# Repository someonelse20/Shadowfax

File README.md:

# Shadowfax
FPV Drone designed from scrach. This design isn't fully custom yet but will get there eventually. I started this project to make a cool drone and learn as much as I can about engineering.

## Flight Controller
The meat and potatios, the main computer for the drone.

## Transceiver
A low frequency radio to communicate with a remote controller.

## Camera Controller
Controls the camera and captures videos and pictures with a high frequency radio for faster communication.

## Power Board
Powers the whole stack with 3.3v and connects the ESCs to the input voltage.

## Frame
I made a custom frame to fit my custom boards and here it is.

## BOM
| Name                       | Purpose                                       | Quantity | Total Cost (USD) | Link               | Distributor |
|----------------------------|-----------------------------------------------|----------|------------------|--------------------|-------------|
| Flight Controller Assembly | Assemble components for the flight controller | 2        | 42.44            | https://jlcpcb.com | JLCPCB      |
| Flight Controller Board    | The pcb for the flight controller             | 5        | 2.00             | https://jlcpcb.com | JLCPCB      |
| Power Board Assembly       | Assemble components for the power board       | 2        | 14.79            | https://jlcpcb.com | JLCPCB      |
| Power Board                | The pcb for the power board                   | 5        | 7.00             | https://jlcpcb.com | JLCPCB      |
| Transceiver Assmebly       | Assemble components for the board             | 2        | 51.31            | https://jlcpcb.com | JLCPCB      |
| Transceiver Board          | The pcb for the transceiver                   | 5        | 7.00             | https://jlcpcb.com | JLCPCB      |
| Camera Controller Assembly | Assemble components for the board             | 2        | 34.63            | https://jlcpcb.com | JLCPCB      |
| Camera Controller Board    | The pcb for the camera controller             | 5        | 7.00             | https://jlcpcb.com | JLCPCB      |

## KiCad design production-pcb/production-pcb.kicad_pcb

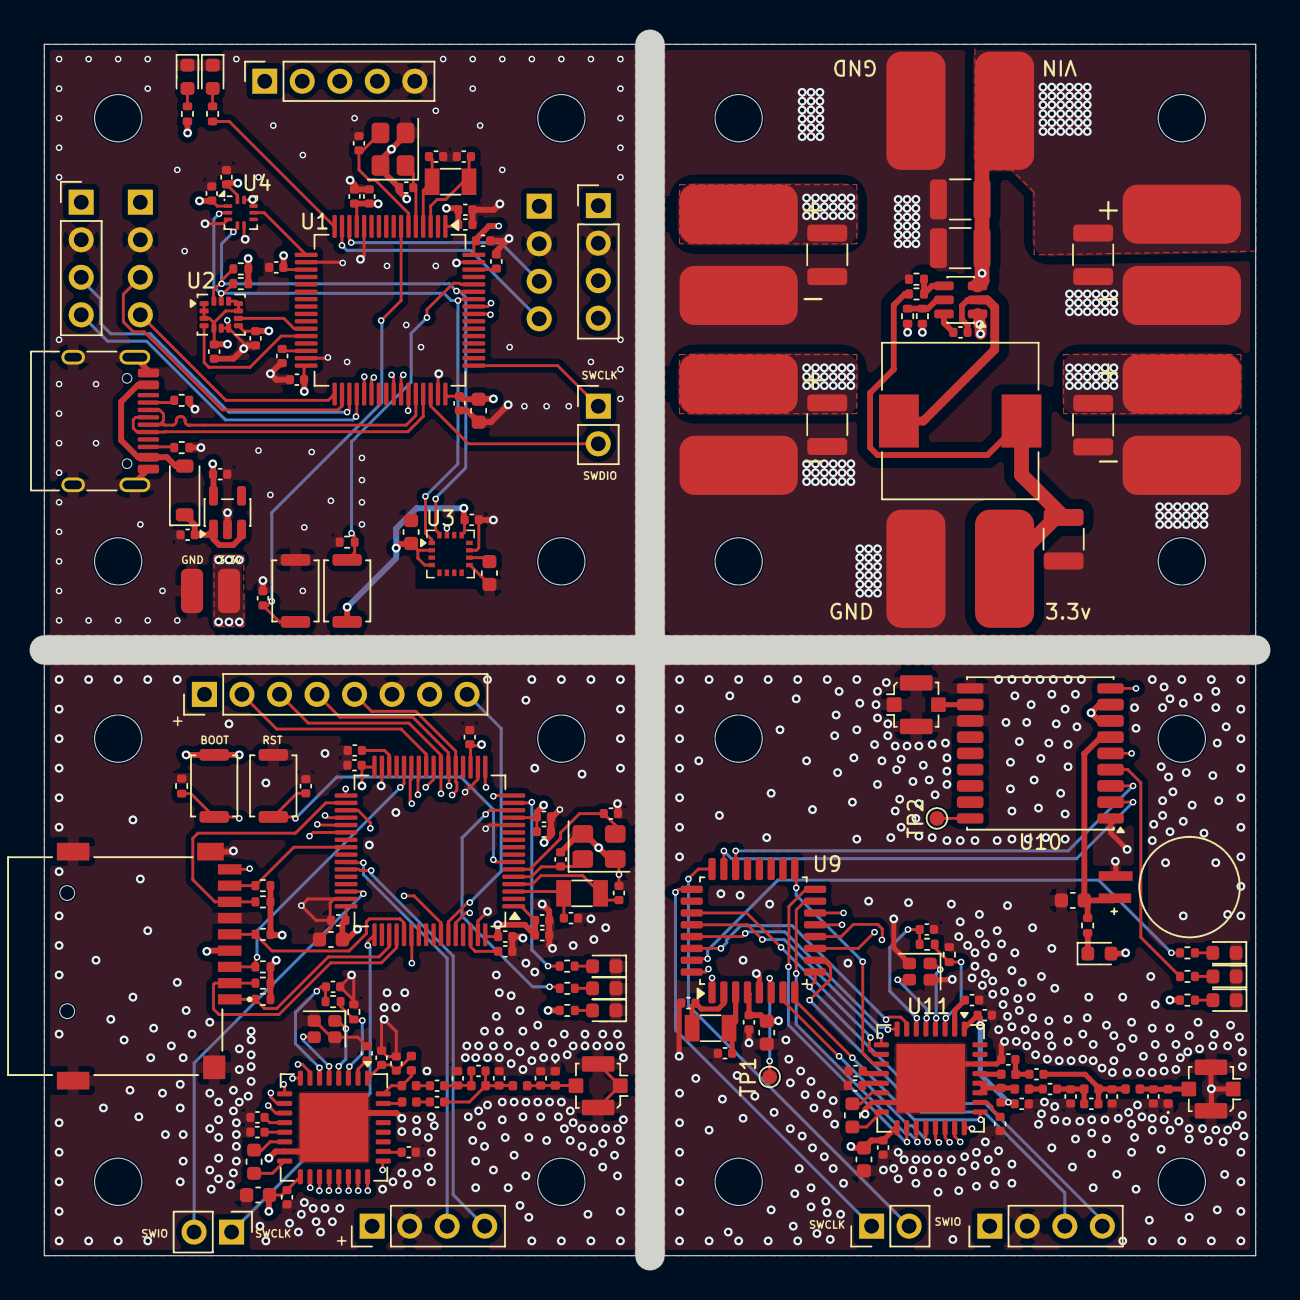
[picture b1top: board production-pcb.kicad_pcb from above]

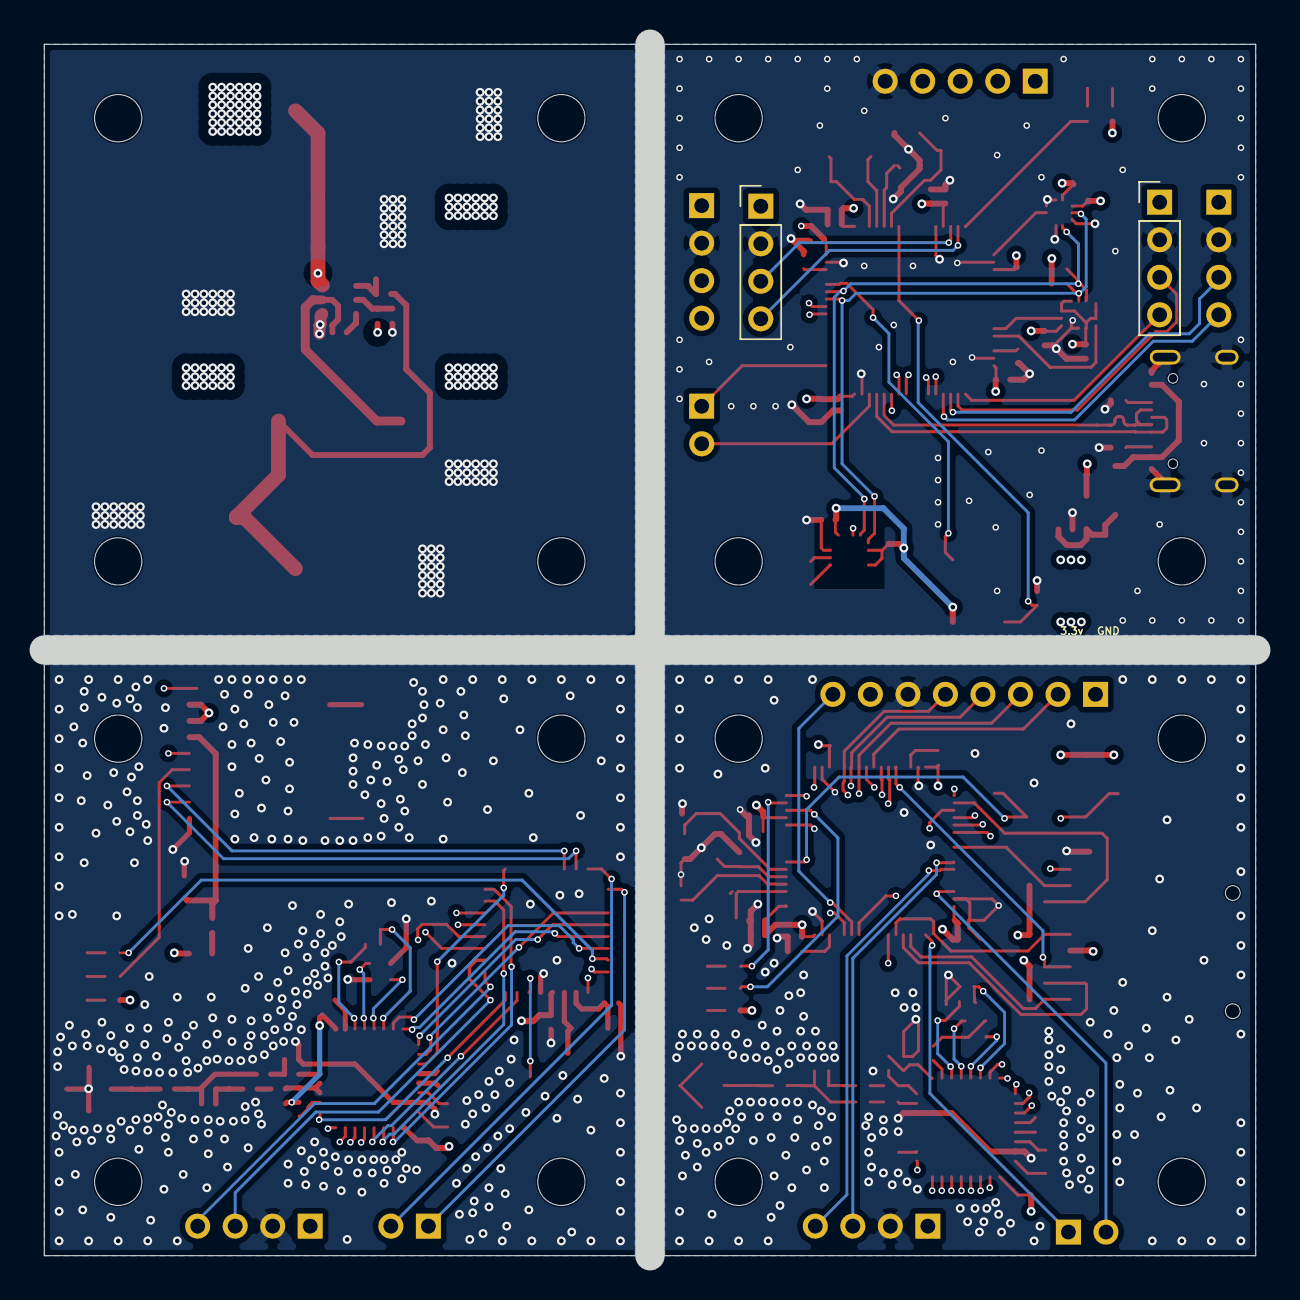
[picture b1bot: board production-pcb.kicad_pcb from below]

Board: 4 copper layers, 82.0 x 82.0 mm, 194 parts (2 on the bottom side), 109 nets.

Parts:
BOOT1, BOOT2: SW_Push; SW_Push_SPST_NO_Alps_SKRK
BT1: MS621FE-FL11E; BAT_MS621FE-FL11E
C1, C74: 1uF; C_0603_1608Metric
C2, C3, C15, C16, C17, C31: 10uF; C_1210_3225Metric
C4, C6, C7, C8, C11, C12, C18, C20, C24, C25, C27, C29, C32, C40, C42, C43, C45, C46, C47, C48, C50, C53, C65, C69, C70: 100nF; C_0402_1005Metric
C5: 10uF; C_0603_1608Metric
C9, C14, C34, C37, C57, C83: 18pF; C_0402_1005Metric
C10, C13, C35, C36: 15pF; C_0402_1005Metric
C19, C21, C22, C23, C41, C44, C61, C63, C75, C76: 1uF; C_0402_1005Metric
C26, C28, C38, C39, C58, C60, C72, C73: 2.2uF; C_0402_1005Metric
C30, C49, C55, C66, C71: 4.7uF; C_0603_1608Metric
C33: 47uF; C_1210_3225Metric
C51, C67, C68, C78: 47pF; C_0402_1005Metric
C52: 6.8pF; C_0402_1005Metric
C54: 2.7pF; C_0402_1005Metric
C56: 1.1pF; C_0402_1005Metric
C59: 1.2pF; C_0402_1005Metric
C62: 2pF; C_0402_1005Metric
C64, C77: 1nF; C_0402_1005Metric
C79: 22pF; C_0402_1005Metric
C80: 2.2pF; C_0402_1005Metric
C81: 7.5pF; C_0402_1005Metric
C82, C85: 1.8pF; C_0402_1005Metric
C84: 3.9pF; C_0402_1005Metric
D1, D2, D4, D5, D6, D9, D10, D11: LED; LED_0603_1608Metric
D3: D_Schottky; D_SOD-123
D7, D12: D_TVS; D_0402_1005Metric
D8: D_Schottky; D_0603_1608Metric
J1: USB_C_Receptacle_USB2.0_14P; USB_C_Receptacle_HRO_TYPE-C-31-M-12
J2, J3, J3#2, J4#2, J5, J22: Conn_01x04; PinHeader_1x04_P2.54mm_Vertical
J4, J7, J24: Conn_01x02; PinHeader_1x02_P2.54mm_Vertical
J6: Conn_01x05; PinSocket_1x05_P2.54mm_Vertical
J8, J9: Conn_01x01; SolderWirePad_1x01_SMD_1.5x3mm
J10, J11, J12, J13, J14, J15, J16, J17, J18, J19, J20, J21: Conn_01x01; SolderWirePad_1x01_SMD_4x8mm
J23: Conn_01x08; PinHeader_1x08_P2.54mm_Vertical
J25: Micro_SD_Card_Det1; CUI_MSD-4-A
J26, J29, J30: Conn_Coaxial; U.FL_Molex_MCRF_73412-0110_Vertical
L1: 10uH; L_10.4x10.4_H4.8
L2: 18nH; L_0402_1005Metric
L3: 1.5nH; L_0402_1005Metric
L4: 1.6nH; L_0402_1005Metric
L5: 1.1nH; L_0402_1005Metric
L6, L8: 2.2uH; L_0603_1608Metric
L7: 2.4nH; L_0402_1005Metric
L9: 12nH; L_0402_1005Metric
L10: 4.7nH; L_0402_1005Metric
L11: 24nH; L_0402_1005Metric
L12: 3.9nH; L_0402_1005Metric
L13: 7.5nH; L_0402_1005Metric
R1, R2: 5.1K; R_0402_1005Metric
R3, R10, R11, R12, R14, R16, R17, R21: 10K; R_0402_1005Metric
R4, R5, R18, R19, R20, R25, R26, R27: 1.2K; R_0402_1005Metric
R6, R8: 100K; R_0402_1005Metric
R7: 33.2K; R_0402_1005Metric
R9: 22K; R_0402_1005Metric
R13, R15, R24: 1K; R_0402_1005Metric
R22, R23: 120K; R_0402_1005Metric
RESET1, RESET2: SW_Push; SW_Push_SPST_NO_Alps_SKRK
TH1, TH2: ERT-J0ER104F; R_0402_1005Metric
TP1, TP2: TestPoint; TestPoint_Pad_D1.0mm
U1, U7: STM32H523RCTx; LQFP-64_10x10mm_P0.5mm
U2: LSM6DSV; LGA-14_3x2.5mm_P0.5mm_LayoutBorder3x4y
U3: MMC5983MA; LGA-16_3x3mm_P0.5mm
U4: BMP384; Rohm_MLGA010V020A_LGA-10_2x2mm_P0.45mm_LayoutBorder2x3y
U5: MIC5504-3.3YM5; SOT-23-5
U6: TPS54308; SOT-23-6
U8, U11: LR2021; QFN-32-1EP_7x7mm_P0.65mm_EP4.65x4.65mm
U9: STM32G030K8Tx; LQFP-32_7x7mm_P0.8mm
U10: MAX-M10S; ublox_MAX
Y1, Y3: 32.768MHz; Crystal_SMD_3215-2Pin_3.2x1.5mm
Y2, Y4: 24MHz; Crystal_SMD_3225-4Pin_3.2x2.5mm
Y5, Y7: 32MHz 10pF; Crystal_SMD_2016-4Pin_2.0x1.6mm
Y6: 32.768KHz; Crystal_SMD_3215-2Pin_3.2x1.5mm

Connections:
+3.3V: BOOT1.1, BOOT2.1, C1.1, C4.1, C6.1, C7.1, C8.1, C12.1, C18.1, C19.1, C20.1, C21.1, C23.1, C24.1, C25.1, C27.1, C29.1, C30.1, C40.1, C41.1, C42.1, C44.1, C45.1, C46.1, C47.1, C48.1, C49.1, C53.1, C55.1, C65.1, C66.1, C70.1, C71.1, D8.2 (A), J2.1, J3.1, J3#2.1, J4#2.1, J5.1, J8.1 (Pin_1_1), J22.1, J23.7, J25.4 (VDD), R4.1, R5.1, R10.1, R11.1, R12.1, R14.1, R15.1, R16.1, R17.1, R18.1, R25.1, U1.1 (VBAT), U1.13 (VDDA), U1.19 (VDD), U1.32 (VDD), U1.48 (VDD), U1.64 (VDD), U2.1 (SDO/SA0), U2.2 (SDX), U2.3 (SCX), U2.5 (VDDIO), U2.8 (VDD), U2.10 (OCS_Aux), U2.11 (SDO_Aux), U2.12 (CS), U3.2 (VDD), U3.4 (SPI_CS), U3.13 (VDDIO), U4.1 (VDDIO), U4.10 (VDD), U5.5 (VOUT), U7.1 (VBAT), U7.13 (VDDA), U7.19 (VDD), U7.32 (VDD), U7.48 (VDD), U7.64 (VDD), U8.17 (VBAT), U9.4 (VDD), U10.7 (VCC_IO), U10.8 (VCC), U11.17 (VBAT)
/BMP_INT: U1.17 (PA3), U4.7 (INT)
/BOOT: BOOT1.2, BOOT2.2, R3.1, R21.1, U1.60 (BOOT0), U7.60 (BOOT0)
/CAM_CS: J23.2, U7.25 (PC5)
/CAM_STAT: R19.1, U7.14 (PA0)
/ESC1: J6.1, U1.41 (PA8)
/ESC2: J6.2, U1.42 (PA9)
/ESC3: J6.3, U1.56 (PB4(NJTRST))
/ESC4: J6.4, U1.57 (PB5)
/GPS_INT: U9.32 (PB8), U10.5 (EXTINT)
/GPS_LED: R26.1, U10.4 (TIMEPULSE)
/GPS_RST: U9.1 (PB9), U10.9 (~RESET)
/GPS_RX: U9.23 (PA10/PA12), U10.2 (TXD)
/GPS_TX: U9.22 (PA9/PA11), U10.3 (RXD)
/HSE_IN: C9.1, C37.1, U1.5 (PH0), U7.5 (PH0), Y2.1, Y4.1
/HSE_OUT: C14.1, C34.1, U1.6 (PH1), U7.6 (PH1), Y2.3, Y4.3
/LMS_INT2: U1.27 (PB1), U2.9 (INT2)
/LR_BUSY: U7.16 (PA2), U8.25 (BUSY), U9.8 (PA1), U11.25 (BUSY)
/LR_CS: U7.17 (PA3), U8.24 (NSS)
/LR_D5: U7.26 (PB0), U8.19 (DIO5), U9.15 (PB0), U11.19 (DIO5)
/LR_D6: U7.27 (PB1), U8.18 (DIO6), U9.16 (PB1), U11.18 (DIO6)
/LR_D7: U7.38 (PC7), U8.11 (DIO7), U9.17 (PB2), U11.11 (DIO7)
/LR_D8: U7.37 (PC6), U8.10 (DIO8), U9.27 (PB3), U11.10 (DIO8)
/LR_D9: U7.36 (PB15), U8.9 (DIO9), U9.28 (PB4), U11.9 (DIO9)
/LR_D10: U7.35 (PB14), U8.8 (DIO10), U9.29 (PB5), U11.8 (DIO10)
/LR_D11: U7.33 (PB12), U8.7 (DIO11), U9.30 (PB6), U11.7 (DIO11)
/LR_RST: U7.24 (PC4), U8.20 (~RESET), U9.7 (PA0), U11.20 (~RESET)
/LR_STAT: R20.1, R27.1, U7.15 (PA1), U9.31 (PB7)
/LSE_IN: C10.1, C35.1, C67.2, U1.3 (PC14), U7.3 (PC14), U9.2 (PC14), Y1.1, Y3.1, Y6.2
/LSE_OUT: C13.1, C36.1, C68.2, U1.4 (PC15), U7.4 (PC15), U9.3 (PC15), Y1.2, Y3.2, Y6.1
/LSM_INT1: U1.28 (PB2), U2.4 (INT1)
/MISO: J23.4, U7.22 (PA6), U8.21 (MISO), U9.13 (PA6), U11.21 (MISO)
/MMC_INT: U1.43 (PA10), U3.15 (INT)
/MOSI: J23.3, U7.23 (PA7), U8.22 (MOSI), U9.14 (PA7), U11.22 (MOSI)
/NSS: U9.11 (PA4), U11.24 (NSS)
/NTC: R22.2, R23.2, TH1.1, TH2.1, U8.3 (NTC), U11.3 (NTC)
/RFI: L7.1, U8.31 (RFI_HF)
/RFI_LF: L11.1, U11.29 (RFI_LF)
/RFO: L2.2, L3.1, U8.32 (RFO_HF)
/RFO_LF1: L9.2, L10.1, U11.27 (RFO_LF2), U11.28 (RFO_LF1)
/SCK: J23.5, U7.21 (PA5), U8.23 (SCK), U9.12 (PA5), U11.23 (SCK)
/SCL: J23.1, R4.2, U1.58 (PB6), U2.13 (SCL), U3.1 (SCL/SPI_SCK), U4.2 (SCK), U7.58 (PB6)
/SDA: J23.8, R5.2, U1.59 (PB7), U2.14 (SDA), U3.16 (SDA/SPI_SDI), U4.4 (SDI), U7.59 (PB7)
/SD_CLK: J25.5 (CLK), R14.2, U7.53 (PC12)
/SD_CMD: J25.3 (CMD), R12.2, U7.28 (PB2)
/SD_D0: J25.7 (DAT0), R16.2, U7.34 (PB13)
/SD_D1: J25.8 (DAT1), R17.2, U7.40 (PC9)
/SD_D2: J25.1 (DAT2), R10.2, U7.51 (PC10)
/SD_D3: J25.2 (DAT3/CD), R11.2, U7.52 (PC11)
/SD_DET: J25.9 (DET), U7.54 (PD2)
/STAT_LED: R13.1, U1.16 (PA2)
/STM32_RST: C11.2, C43.2, RESET1.2, RESET2.2, U1.7 (NRST), U7.7 (NRST)
/SWCLK: J4.1, J7.1, J24.1, U1.49 (PA14(JTCK), U7.49 (PA14(JTCK), U9.25 (PA14)
/SWDIO: J4.2, J7.2, J24.2, U1.46 (PA13(JTMS), U7.46 (PA13(JTMS), U9.24 (PA13)
/UART_RX: J3.3, J22.3, U7.42 (PA9), U9.10 (PA3)
/UART_RX1: J2.4, U1.36 (PB15)
/UART_RX4: J4#2.4, U1.15 (PA1)
/UART_RX5: J3#2.4, U1.33 (PB12)
/UART_RX6: J5.4, U1.38 (PC7)
/UART_TX: J3.4, J22.4, U7.43 (PA10), U9.9 (PA2)
/UART_TX1: J2.3, U1.35 (PB14)
/UART_TX4: J4#2.3, U1.14 (PA0)
/UART_TX5: J3#2.3, U1.34 (PB13)
/UART_TX6: J5.3, U1.37 (PC6)
/USB_+: J1.A6 (D+), J1.B6 (D+), U1.45 (PA12), U7.45 (PA12)
/USB_-: J1.A7 (D-), J1.B7 (D-), U1.44 (PA11), U7.44 (PA11)
/VDCC1: C63.1, C76.1, U8.12 (VDCC1), U11.12 (VDCC1)
/VDCC2: C61.1, C75.1, U8.26 (VDCC2), U11.26 (VDCC2)
/VNTC: C50.1, C69.1, R22.1, R23.1, U8.6 (VTCXO/VNTC), U11.6 (VTCXO/VNTC)
/VPAX1: C60.1, C73.1, U8.13 (VPAX1), U11.13 (VPAX1)
/VPAX2: C58.1, C72.1, U8.2 (VPAX2), U11.2 (VPAX2)
/VR_PA: C51.1, C64.1, C77.1, C78.1, L2.1, L9.1, U8.1 (VR_PA), U11.1 (VR_PA)
/V_BCKP: BT1.1 (+), C74.1, R24.2, U10.6 (V_BCKP)
GND: BT1.2 (-), C1.2, C2.2, C3.2, C4.2, C5.2, C6.2, C7.2, C8.2, C9.2, C10.2, C11.1, C12.2, C13.2, C14.2, C15.2, C16.2, C17.2, C18.2, C19.2, C20.2, C21.2, C22.2, C23.2, C24.2, C25.2, C26.2, C27.2, C28.2, C29.2, C30.2, C31.2, C33.2, C34.2, C35.2, C36.2, C37.2, C38.2, C39.2, C40.2, C41.2, C42.2, C43.1, C44.2, C45.2, C46.2, C47.2, C48.2, C49.2, C50.2, C51.2, C53.2, C54.2, C55.2, C58.2, C59.2, C60.2, C61.2, C62.2, C63.2, C64.2, C65.2, C66.2, C67.1, C68.1, C69.2, C70.2, C71.2, C72.2, C73.2, C74.2, C75.2, C76.2, C77.2, C78.2, C80.2, C81.2, C84.2, C85.2, D1.1 (K), D2.1 (K), D4.1 (K), D5.1 (K), D6.1 (K), D7.1 (A1), D9.1 (K), D10.1 (K), D11.1 (K), D12.1 (A1), J1.A1 (GND), J1.A12 (GND), J1.B1 (GND), J1.B12 (GND), J1.SH (SHIELD), J2.2, J3.2, J3#2.2, J4#2.2, J5.2, J6.5, J9.1 (Pin_1_1), J11.1 (Pin_1_1), J13.1 (Pin_1_1), J15.1 (Pin_1_1), J17.1 (Pin_1_1), J19.1 (Pin_1_1), J21.1 (Pin_1_1), J22.2, J23.6, J25.6 (VSS), J25.SH (SHIELD), J26.2 (Ext), J29.2 (Ext), J30.2 (Ext), R1.2, R2.1, R3.2, R7.2, R9.2, R21.2, RESET1.1, RESET2.1, TH1.2, TH2.2, U1.12 (VSSA), U1.18 (VSS), U1.31 (VSS), U1.47 (VSS), U1.63 (VSS), U2.6 (GND), U2.7 (GND), U3.9 (GND), U3.11 (GND), U4.3 (VSS), U4.5 (SDO), U4.8 (VSS), U4.9 (VSS), U5.2 (GND), U6.1 (GND), U7.12 (VSSA), U7.18 (VSS), U7.31 (VSS), U7.47 (VSS), U7.63 (VSS), U8.15 (GND_DCC), U8.30 (GND), U8.33 (GND), U9.5 (VSS), U10.1 (GND), U10.10 (GND), U10.12 (GND), U11.15 (GND_DCC), U11.30 (GND), U11.33 (GND), Y2.2, Y2.4, Y4.2, Y4.4, Y5.2 (G), Y5.4 (G), Y7.2 (G), Y7.4 (G)
unnamed: C52.1, L3.2
unnamed: C52.2, C54.1, C56.1, L4.2
unnamed: C79.1, L10.2
unnamed: C79.2, C81.1, C82.1, L12.2
unnamed: C82.2, C83.2, C84.1, L12.1, L13.1
unnamed: C57.1, L7.2
unnamed: C56.2, C57.2, C59.1, L4.1, L5.1
unnamed: C80.1, C83.1, L11.2
unnamed: C26.1, C39.1, U1.62 (VCAP), U7.62 (VCAP)
unnamed: C28.1, C38.1, U1.30 (VCAP), U7.30 (VCAP)
unnamed: C62.1, D7.2 (A2), J26.1 (In), L5.2
unnamed: D1.2 (A), R15.2
unnamed: C85.1, D12.2 (A2), J30.1 (In), L13.2
unnamed: D2.2 (A), R13.2
unnamed: D3.2 (A), D4.2 (A), J1.A4 (VBUS), J1.A9 (VBUS), J1.B4 (VBUS), J1.B9 (VBUS), R18.2
unnamed: C22.1, D3.1 (K), D8.1 (K), R24.1, U5.1 (VIN), U5.3 (EN)
unnamed: D5.2 (A), D9.2 (A), R19.2, R25.2
unnamed: D6.2 (A), D10.2 (A), R20.2, R26.2
unnamed: D11.2 (A), R27.2
unnamed: J1.A5 (CC1), R1.1
unnamed: J1.B5 (CC2), R2.2
unnamed: C33.1, J20.1 (Pin_1_1), L1.2, R8.1
unnamed: J29.1 (In), U10.11 (RF_IN)
unnamed: C32.1, U6.6 (BOOT)
unnamed: R6.2, R7.1, U6.5 (EN)
unnamed: R8.2, R9.1, U6.4 (FB)
unnamed: C32.2, L1.1, U6.2 (SW)
unnamed: L6.1, L8.1, U8.16 (LXA), U11.16 (LXA)
unnamed: L6.2, L8.2, U8.14 (LXB), U11.14 (LXB)
unnamed: U8.4 (XTA), U11.4 (XTA), Y5.1, Y7.1
unnamed: U8.5 (XTB), U11.5 (XTB), Y5.3, Y7.3
unnamed: C5.1, U3.10 (CAP)
unnamed: TP1.1 (1_1), U9.6 (NRST)
unnamed: TP2.1 (1_1), U10.18 (~SAFEBOOT)
VBUS: C2.1, C3.1, C15.1, C16.1, C17.1, C31.1, J10.1 (Pin_1_1), J12.1 (Pin_1_1), J14.1 (Pin_1_1), J16.1 (Pin_1_1), J18.1 (Pin_1_1), R6.1, U6.3 (VIN)

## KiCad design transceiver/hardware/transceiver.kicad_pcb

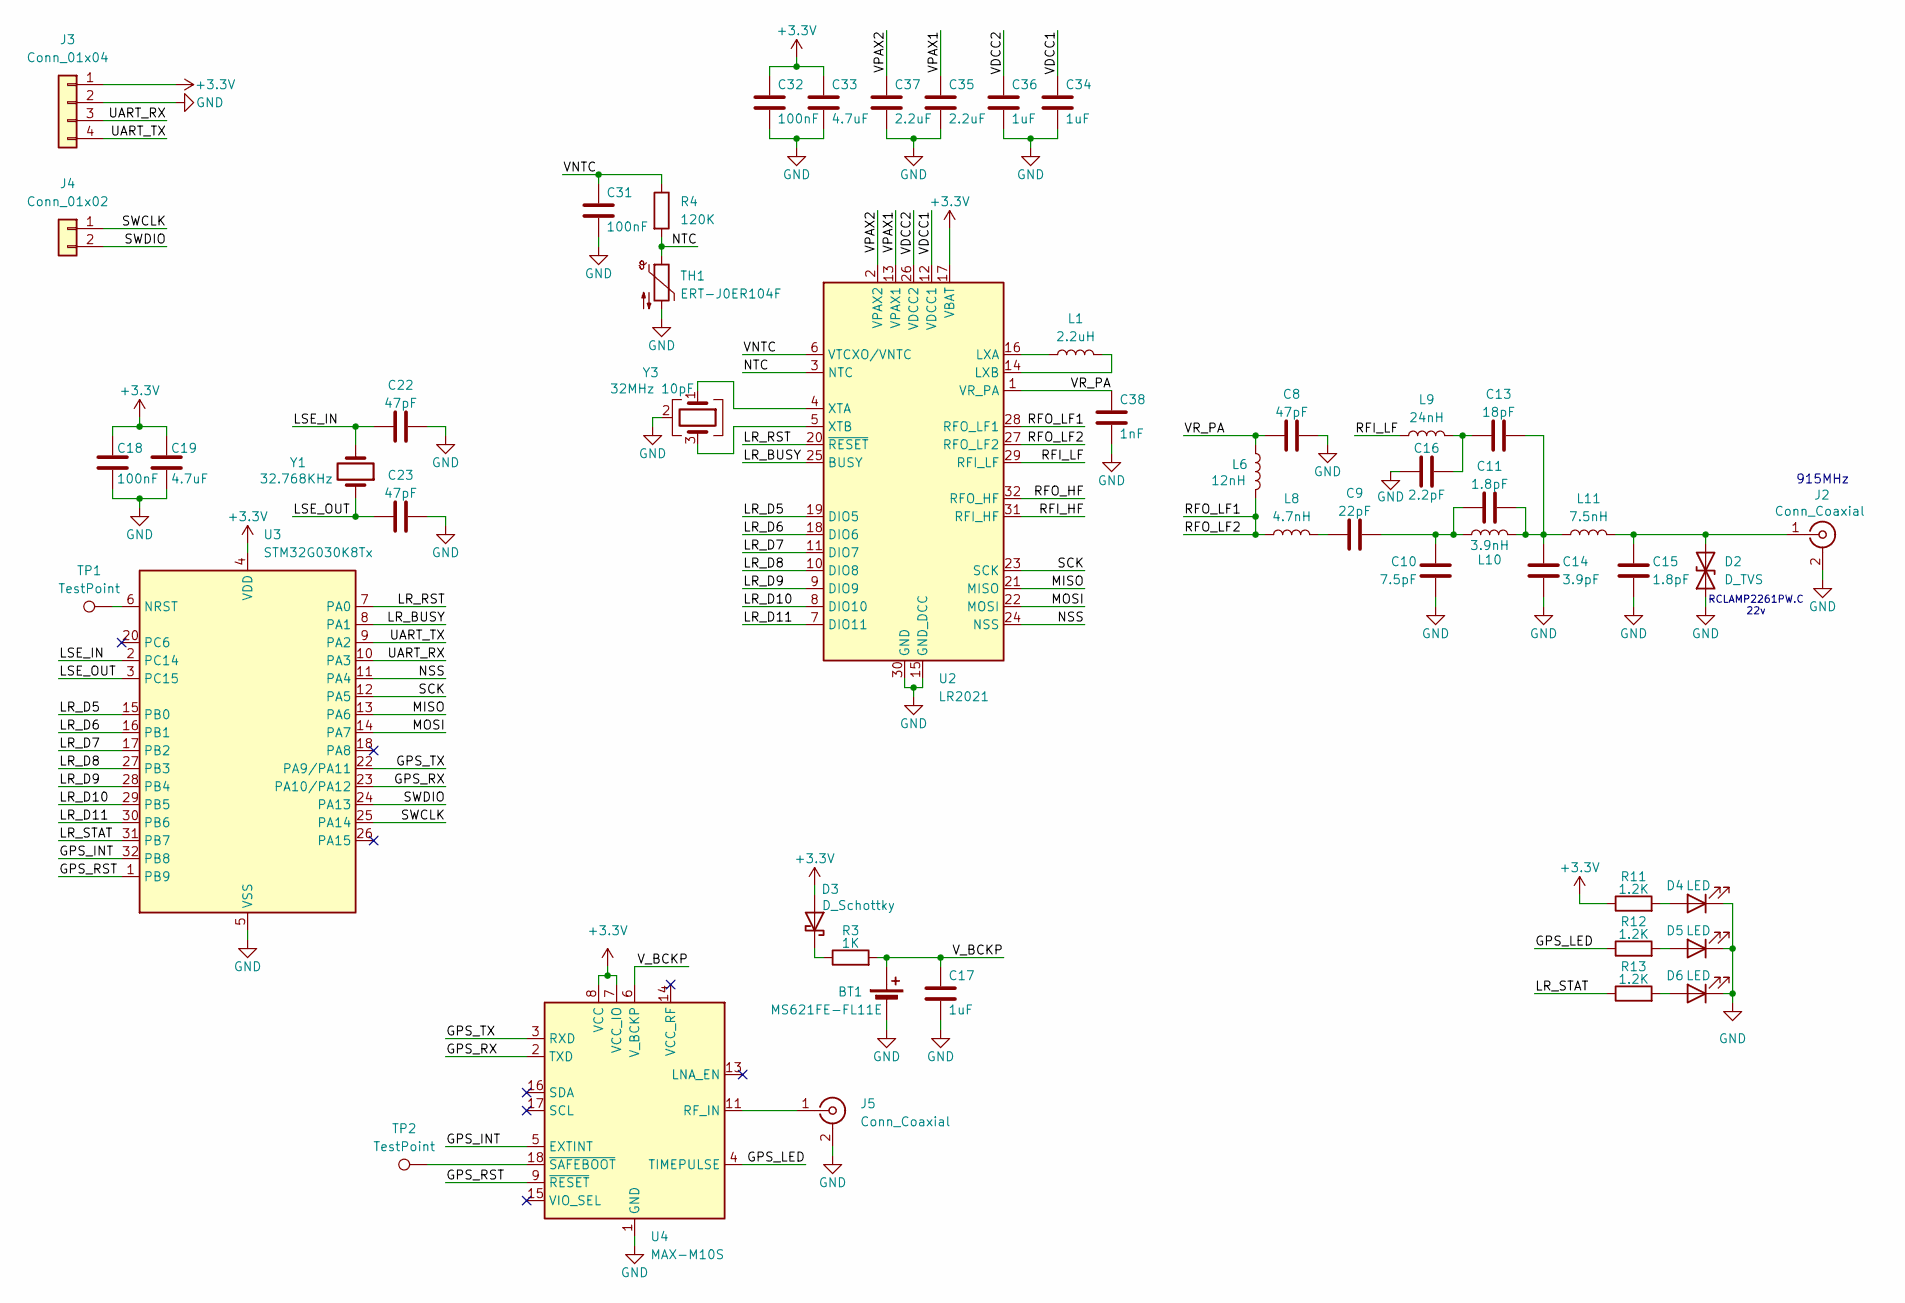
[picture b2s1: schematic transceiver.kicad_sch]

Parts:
BT1: MS621FE-FL11E; BAT_MS621FE-FL11E
C8, C22, C23: 47pF; C_0402_1005Metric
C9: 22pF; C_0402_1005Metric
C10: 7.5pF; C_0402_1005Metric
C11, C15: 1.8pF; C_0402_1005Metric
C13: 18pF; C_0402_1005Metric
C14: 3.9pF; C_0402_1005Metric
C16: 2.2pF; C_0402_1005Metric
C17: 1uF; C_0603_1608Metric
C18, C31, C32: 100nF; C_0402_1005Metric
C19, C33: 4.7uF; C_0603_1608Metric
C34, C36: 1uF; C_0402_1005Metric
C35, C37: 2.2uF; C_0402_1005Metric
C38: 1nF; C_0402_1005Metric
D2: D_TVS; D_0402_1005Metric
D3: D_Schottky; D_0603_1608Metric
D4, D5, D6: LED; LED_0603_1608Metric
J2, J5: Conn_Coaxial; U.FL_Molex_MCRF_73412-0110_Vertical
J3: Conn_01x04; PinHeader_1x04_P2.54mm_Vertical
J4: Conn_01x02; PinHeader_1x02_P2.54mm_Vertical
L1: 2.2uH; L_0603_1608Metric
L6: 12nH; L_0402_1005Metric
L8: 4.7nH; L_0402_1005Metric
L9: 24nH; L_0402_1005Metric
L10: 3.9nH; L_0402_1005Metric
L11: 7.5nH; L_0402_1005Metric
R3: 1K; R_0402_1005Metric
R4: 120K; R_0402_1005Metric
R11, R12, R13: 1.2K; R_0402_1005Metric
TH1: ERT-J0ER104F; R_0402_1005Metric
TP1, TP2: TestPoint; TestPoint_Pad_D1.0mm
U2: LR2021; QFN-32-1EP_7x7mm_P0.65mm_EP4.65x4.65mm
U3: STM32G030K8Tx; LQFP-32_7x7mm_P0.8mm
U4: MAX-M10S; ublox_MAX
Y1: 32.768KHz; Crystal_SMD_3215-2Pin_3.2x1.5mm
Y3: 32MHz 10pF; Crystal_SMD_2016-4Pin_2.0x1.6mm

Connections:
+3.3V: C18.1, C19.1, C32.1, C33.1, D3.2 (A), J3.1, R11.1, U2.17 (VBAT), U3.4 (VDD), U4.7 (VCC_IO), U4.8 (VCC)
/GPS_INT: U3.32 (PB8), U4.5 (EXTINT)
/GPS_LED: R12.1, U4.4 (TIMEPULSE)
/GPS_RST: U3.1 (PB9), U4.9 (~RESET)
/GPS_RX: U3.23 (PA10/PA12), U4.2 (TXD)
/GPS_TX: U3.22 (PA9/PA11), U4.3 (RXD)
/LR_BUSY: U2.25 (BUSY), U3.8 (PA1)
/LR_D5: U2.19 (DIO5), U3.15 (PB0)
/LR_D6: U2.18 (DIO6), U3.16 (PB1)
/LR_D7: U2.11 (DIO7), U3.17 (PB2)
/LR_D8: U2.10 (DIO8), U3.27 (PB3)
/LR_D9: U2.9 (DIO9), U3.28 (PB4)
/LR_D10: U2.8 (DIO10), U3.29 (PB5)
/LR_D11: U2.7 (DIO11), U3.30 (PB6)
/LR_RST: U2.20 (~RESET), U3.7 (PA0)
/LR_STAT: R13.1, U3.31 (PB7)
/LSE_IN: C22.2, U3.2 (PC14), Y1.2
/LSE_OUT: C23.2, U3.3 (PC15), Y1.1
/MISO: U2.21 (MISO), U3.13 (PA6)
/MOSI: U2.22 (MOSI), U3.14 (PA7)
/NSS: U2.24 (NSS), U3.11 (PA4)
/NTC: R4.2, TH1.1, U2.3 (NTC)
/RFI_HF: U2.31 (RFI_HF)
/RFI_LF: L9.1, U2.29 (RFI_LF)
/RFO_HF: U2.32 (RFO_HF)
/RFO_LF1: L6.2, L8.1, U2.27 (RFO_LF2), U2.28 (RFO_LF1)
/SCK: U2.23 (SCK), U3.12 (PA5)
/SWCLK: J4.1, U3.25 (PA14)
/SWDIO: J4.2, U3.24 (PA13)
/UART_RX: J3.3, U3.10 (PA3)
/UART_TX: J3.4, U3.9 (PA2)
/VDCC1: C34.1, U2.12 (VDCC1)
/VDCC2: C36.1, U2.26 (VDCC2)
/VNTC: C31.1, R4.1, U2.6 (VTCXO/VNTC)
/VPAX1: C35.1, U2.13 (VPAX1)
/VPAX2: C37.1, U2.2 (VPAX2)
/VR_PA: C8.1, C38.1, L6.1, U2.1 (VR_PA)
/V_BCKP: BT1.1 (+), C17.1, R3.2, U4.6 (V_BCKP)
GND: BT1.2 (-), C8.2, C10.2, C14.2, C15.2, C16.2, C17.2, C18.2, C19.2, C22.1, C23.1, C31.2, C32.2, C33.2, C34.2, C35.2, C36.2, C37.2, C38.2, D2.1 (A1), D4.1 (K), D5.1 (K), D6.1 (K), J2.2 (Ext), J3.2, J5.2 (Ext), TH1.2, U2.15 (GND_DCC), U2.30 (GND), U2.33 (GND), U3.5 (VSS), U4.1 (GND), U4.10 (GND), U4.12 (GND), Y3.2 (G), Y3.4 (G)
unnamed: C9.1, L8.2
unnamed: C9.2, C10.1, C11.1, L10.2
unnamed: C11.2, C13.2, C14.1, L10.1, L11.1
unnamed: C13.1, C16.1, L9.2
unnamed: C15.1, D2.2 (A2), J2.1 (In), L11.2
unnamed: D3.1 (K), R3.1
unnamed: D4.2 (A), R11.2
unnamed: D5.2 (A), R12.2
unnamed: D6.2 (A), R13.2
unnamed: J5.1 (In), U4.11 (RF_IN)
unnamed: L1.1, U2.16 (LXA)
unnamed: L1.2, U2.14 (LXB)
unnamed: U2.4 (XTA), Y3.1
unnamed: U2.5 (XTB), Y3.3
unnamed: TP1.1 (1_1), U3.6 (NRST)
unnamed: TP2.1 (1_1), U4.18 (~SAFEBOOT)

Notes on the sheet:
915MHz
RCLAMP2261PW.C 22v

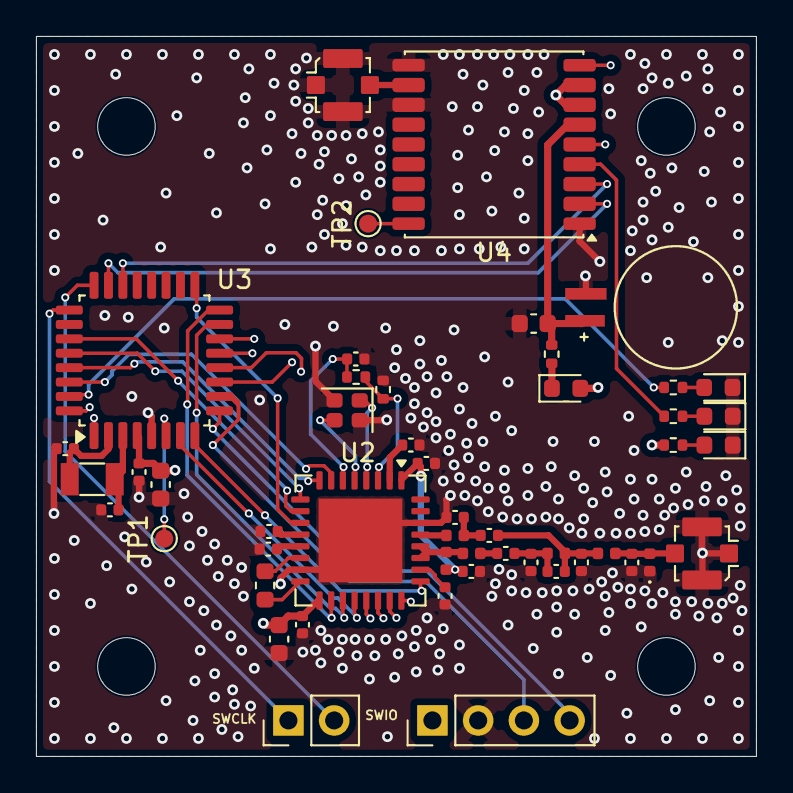
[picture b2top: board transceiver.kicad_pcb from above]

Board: 4 copper layers, 40.0 x 40.0 mm, 50 parts (0 on the bottom side), 53 nets.

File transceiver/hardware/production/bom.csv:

Designator,Footprint,Quantity,Value,LCSC Part #
BT1,BAT_MS621FE-FL11E,1,MS621FE-FL11E,
C10,0402,1,7.5pF,
"C11, C15",0402,2,1.8pF,
C13,0402,1,18pF,
C14,0402,1,3.9pF,
C16,0402,1,2.2pF,
C17,0603,1,1uF,
"C18, C31, C32",0402,3,100nF,
"C19, C33",0603,2,4.7uF,
"C22, C23, C8",0402,3,47pF,
"C34, C36",0402,2,1uF,
"C35, C37",0402,2,2.2uF,
C38,0402,1,1nF,
C9,0402,1,22pF,
D2,0402,1,D_TVS,
D3,0603,1,D_Schottky,
"D4, D5, D6",0603,3,LED,
"J2, J5",U.FL_Molex_MCRF_73412-0110_Vertical,2,Conn_Coaxial,
J3,PinHeader_1x04_P2.54mm_Vertical,1,Conn_01x04,
J4,PinHeader_1x02_P2.54mm_Vertical,1,Conn_01x02,
L1,0603,1,2.2uH,
L10,0402,1,3.9nH,
L11,0402,1,7.5nH,
L6,0402,1,12nH,
L8,0402,1,4.7nH,
L9,0402,1,24nH,
"R11, R12, R13",0402,3,1.2K,
R3,0402,1,1K,
R4,0402,1,120K,
TH1,0402,1,ERT-J0ER104F,
"TP1, TP2",TestPoint_Pad_D1.0mm,2,TestPoint,
U2,QFN-32-1EP_7x7mm_P0.65mm_EP4.65x4.65mm,1,LR2021,
U3,LQFP-32_7x7mm_P0.8mm,1,STM32G030K8Tx,
U4,ublox_MAX,1,MAX-M10S,
Y1,Crystal_SMD_3215-2Pin_3.2x1.5mm,1,32.768KHz,
Y3,Crystal_SMD_2016-4Pin_2.0x1.6mm,1,32MHz 10pF,

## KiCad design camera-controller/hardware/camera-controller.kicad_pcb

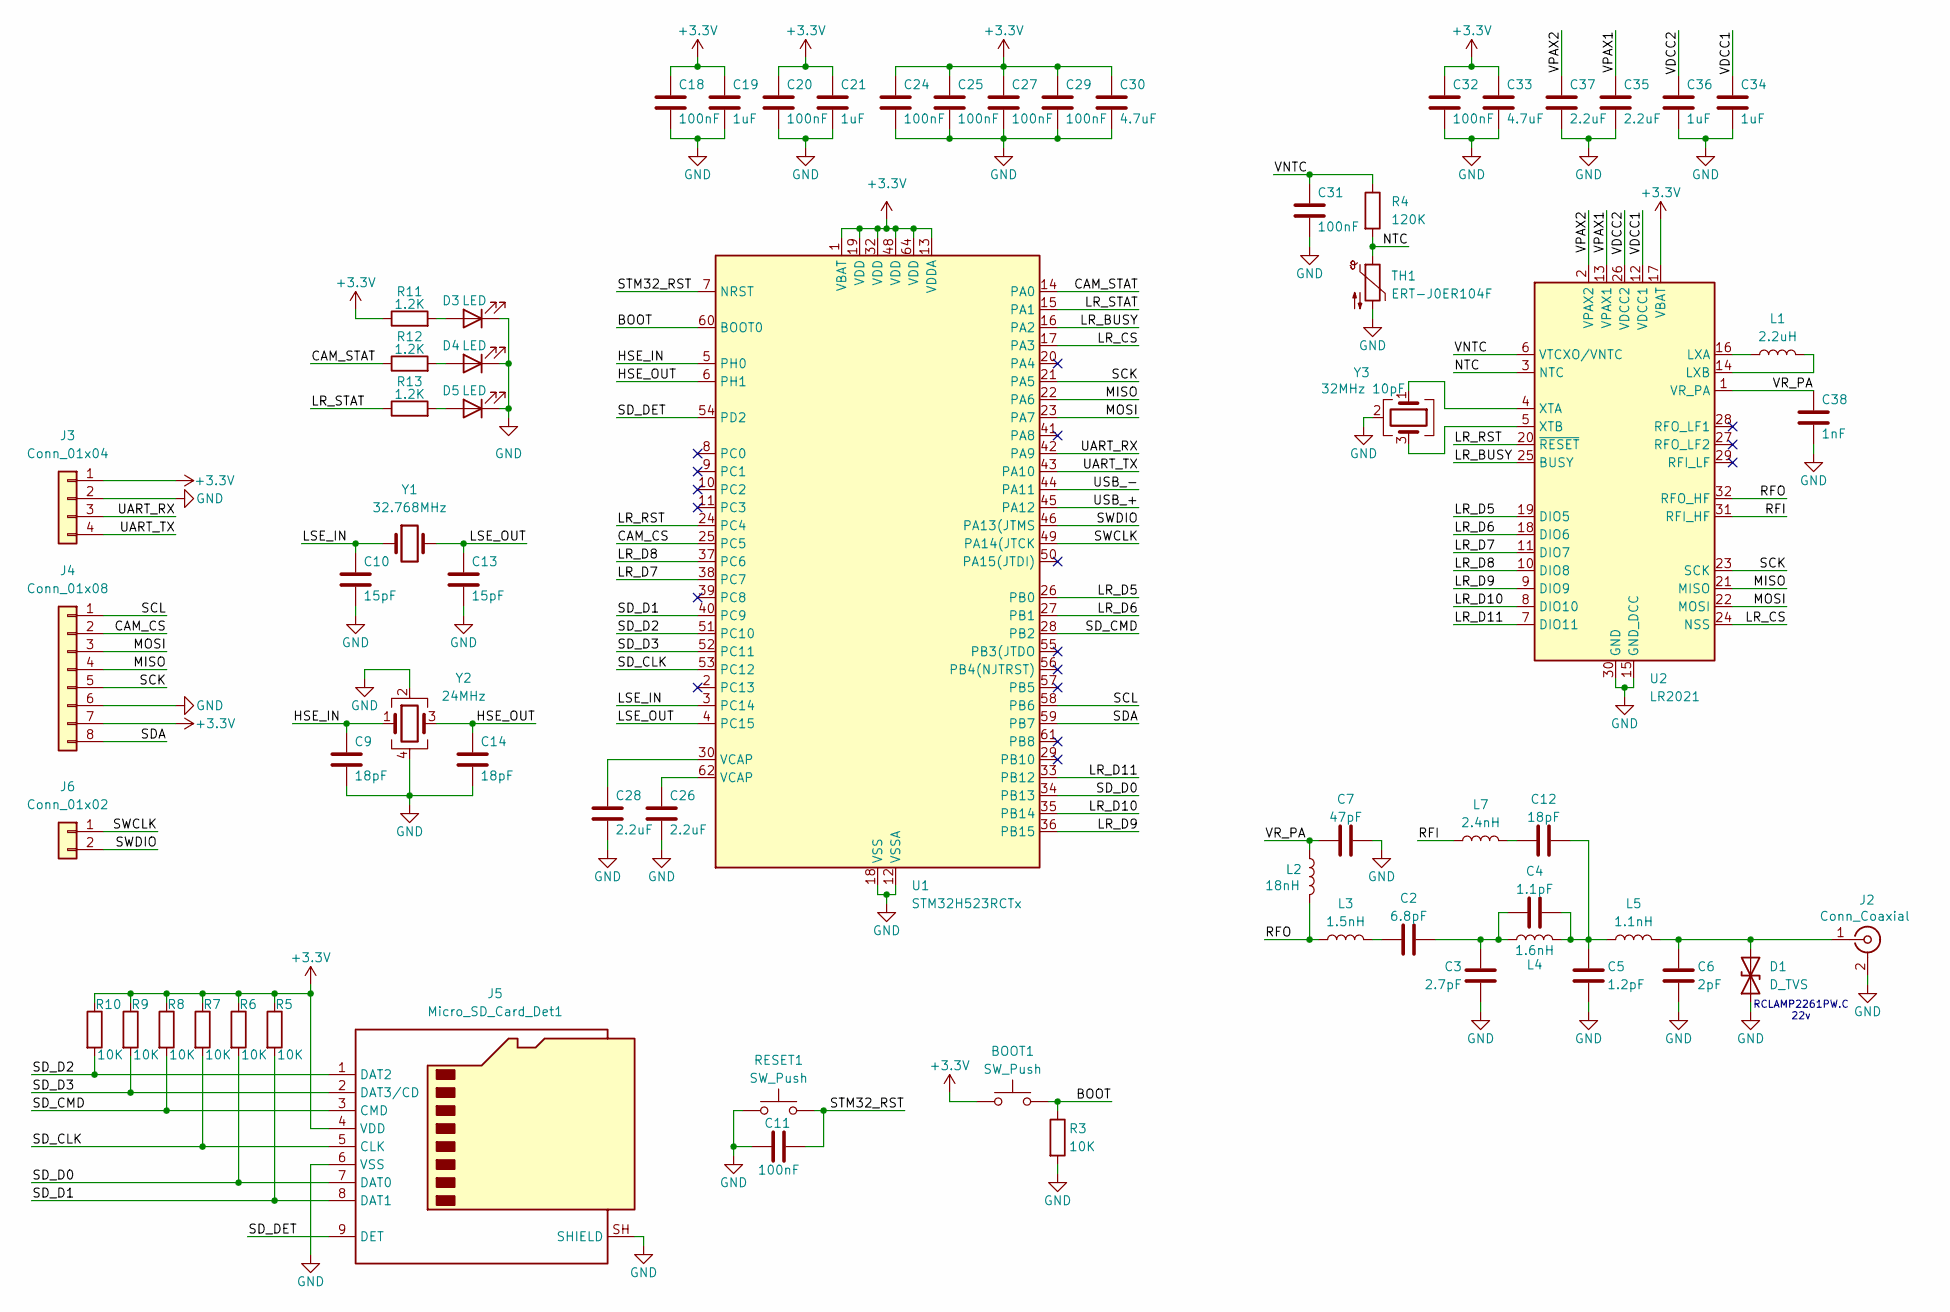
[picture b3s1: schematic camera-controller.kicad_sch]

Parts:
BOOT1: SW_Push; SW_Push_SPST_NO_Alps_SKRK
C2: 6.8pF; C_0402_1005Metric
C3: 2.7pF; C_0402_1005Metric
C4: 1.1pF; C_0402_1005Metric
C5: 1.2pF; C_0402_1005Metric
C6: 2pF; C_0402_1005Metric
C7: 47pF; C_0402_1005Metric
C9, C12, C14: 18pF; C_0402_1005Metric
C10, C13: 15pF; C_0402_1005Metric
C11, C18, C20, C24, C25, C27, C29, C31, C32: 100nF; C_0402_1005Metric
C19, C21, C34, C36: 1uF; C_0402_1005Metric
C26, C28, C35, C37: 2.2uF; C_0402_1005Metric
C30, C33: 4.7uF; C_0603_1608Metric
C38: 1nF; C_0402_1005Metric
D1: D_TVS; D_0402_1005Metric
D3, D4, D5: LED; LED_0603_1608Metric
J2: Conn_Coaxial; U.FL_Molex_MCRF_73412-0110_Vertical
J3: Conn_01x04; PinHeader_1x04_P2.54mm_Vertical
J4: Conn_01x08; PinHeader_1x08_P2.54mm_Vertical
J5: Micro_SD_Card_Det1; CUI_MSD-4-A
J6: Conn_01x02; PinHeader_1x02_P2.54mm_Vertical
L1: 2.2uH; L_0603_1608Metric
L2: 18nH; L_0402_1005Metric
L3: 1.5nH; L_0402_1005Metric
L4: 1.6nH; L_0402_1005Metric
L5: 1.1nH; L_0402_1005Metric
L7: 2.4nH; L_0402_1005Metric
R3, R5, R6, R7, R8, R9, R10: 10K; R_0402_1005Metric
R4: 120K; R_0402_1005Metric
R11, R12, R13: 1.2K; R_0402_1005Metric
RESET1: SW_Push; SW_Push_SPST_NO_Alps_SKRK
TH1: ERT-J0ER104F; R_0402_1005Metric
U1: STM32H523RCTx; LQFP-64_10x10mm_P0.5mm
U2: LR2021; QFN-32-1EP_7x7mm_P0.65mm_EP4.65x4.65mm
Y1: 32.768MHz; Crystal_SMD_3215-2Pin_3.2x1.5mm
Y2: 24MHz; Crystal_SMD_3225-4Pin_3.2x2.5mm
Y3: 32MHz 10pF; Crystal_SMD_2016-4Pin_2.0x1.6mm

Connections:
+3.3V: BOOT1.1, C18.1, C19.1, C20.1, C21.1, C24.1, C25.1, C27.1, C29.1, C30.1, C32.1, C33.1, J3.1, J4.7, J5.4 (VDD), R5.1, R6.1, R7.1, R8.1, R9.1, R10.1, R11.1, U1.1 (VBAT), U1.13 (VDDA), U1.19 (VDD), U1.32 (VDD), U1.48 (VDD), U1.64 (VDD), U2.17 (VBAT)
/BOOT: BOOT1.2, R3.1, U1.60 (BOOT0)
/CAM_CS: J4.2, U1.25 (PC5)
/CAM_STAT: R12.1, U1.14 (PA0)
/HSE_IN: C9.1, U1.5 (PH0), Y2.1
/HSE_OUT: C14.1, U1.6 (PH1), Y2.3
/LR_BUSY: U1.16 (PA2), U2.25 (BUSY)
/LR_CS: U1.17 (PA3), U2.24 (NSS)
/LR_D5: U1.26 (PB0), U2.19 (DIO5)
/LR_D6: U1.27 (PB1), U2.18 (DIO6)
/LR_D7: U1.38 (PC7), U2.11 (DIO7)
/LR_D8: U1.37 (PC6), U2.10 (DIO8)
/LR_D9: U1.36 (PB15), U2.9 (DIO9)
/LR_D10: U1.35 (PB14), U2.8 (DIO10)
/LR_D11: U1.33 (PB12), U2.7 (DIO11)
/LR_RST: U1.24 (PC4), U2.20 (~RESET)
/LR_STAT: R13.1, U1.15 (PA1)
/LSE_IN: C10.1, U1.3 (PC14), Y1.1
/LSE_OUT: C13.1, U1.4 (PC15), Y1.2
/MISO: J4.4, U1.22 (PA6), U2.21 (MISO)
/MOSI: J4.3, U1.23 (PA7), U2.22 (MOSI)
/NTC: R4.2, TH1.1, U2.3 (NTC)
/RFI: L7.1, U2.31 (RFI_HF)
/RFO: L2.2, L3.1, U2.32 (RFO_HF)
/SCK: J4.5, U1.21 (PA5), U2.23 (SCK)
/SCL: J4.1, U1.58 (PB6)
/SDA: J4.8, U1.59 (PB7)
/SD_CLK: J5.5 (CLK), R7.2, U1.53 (PC12)
/SD_CMD: J5.3 (CMD), R8.2, U1.28 (PB2)
/SD_D0: J5.7 (DAT0), R6.2, U1.34 (PB13)
/SD_D1: J5.8 (DAT1), R5.2, U1.40 (PC9)
/SD_D2: J5.1 (DAT2), R10.2, U1.51 (PC10)
/SD_D3: J5.2 (DAT3/CD), R9.2, U1.52 (PC11)
/SD_DET: J5.9 (DET), U1.54 (PD2)
/STM32_RST: C11.2, RESET1.2, U1.7 (NRST)
/SWCLK: J6.1, U1.49 (PA14(JTCK)
/SWDIO: J6.2, U1.46 (PA13(JTMS)
/UART_RX: J3.3, U1.42 (PA9)
/UART_TX: J3.4, U1.43 (PA10)
/USB_+: U1.45 (PA12)
/USB_-: U1.44 (PA11)
/VDCC1: C34.1, U2.12 (VDCC1)
/VDCC2: C36.1, U2.26 (VDCC2)
/VNTC: C31.1, R4.1, U2.6 (VTCXO/VNTC)
/VPAX1: C35.1, U2.13 (VPAX1)
/VPAX2: C37.1, U2.2 (VPAX2)
/VR_PA: C7.1, C38.1, L2.1, U2.1 (VR_PA)
GND: C3.2, C5.2, C6.2, C7.2, C9.2, C10.2, C11.1, C13.2, C14.2, C18.2, C19.2, C20.2, C21.2, C24.2, C25.2, C26.2, C27.2, C28.2, C29.2, C30.2, C31.2, C32.2, C33.2, C34.2, C35.2, C36.2, C37.2, C38.2, D1.1 (A1), D3.1 (K), D4.1 (K), D5.1 (K), J2.2 (Ext), J3.2, J4.6, J5.6 (VSS), J5.SH (SHIELD), R3.2, RESET1.1, TH1.2, U1.12 (VSSA), U1.18 (VSS), U1.31 (VSS), U1.47 (VSS), U1.63 (VSS), U2.15 (GND_DCC), U2.30 (GND), U2.33 (GND), Y2.2, Y2.4, Y3.2 (G), Y3.4 (G)
unnamed: C2.1, L3.2
unnamed: C2.2, C3.1, C4.1, L4.2
unnamed: C12.1, L7.2
unnamed: C4.2, C5.1, C12.2, L4.1, L5.1
unnamed: C26.1, U1.62 (VCAP)
unnamed: C28.1, U1.30 (VCAP)
unnamed: C6.1, D1.2 (A2), J2.1 (In), L5.2
unnamed: D3.2 (A), R11.2
unnamed: D4.2 (A), R12.2
unnamed: D5.2 (A), R13.2
unnamed: L1.1, U2.16 (LXA)
unnamed: L1.2, U2.14 (LXB)
unnamed: U2.4 (XTA), Y3.1
unnamed: U2.5 (XTB), Y3.3

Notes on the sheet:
RCLAMP2261PW.C 22v

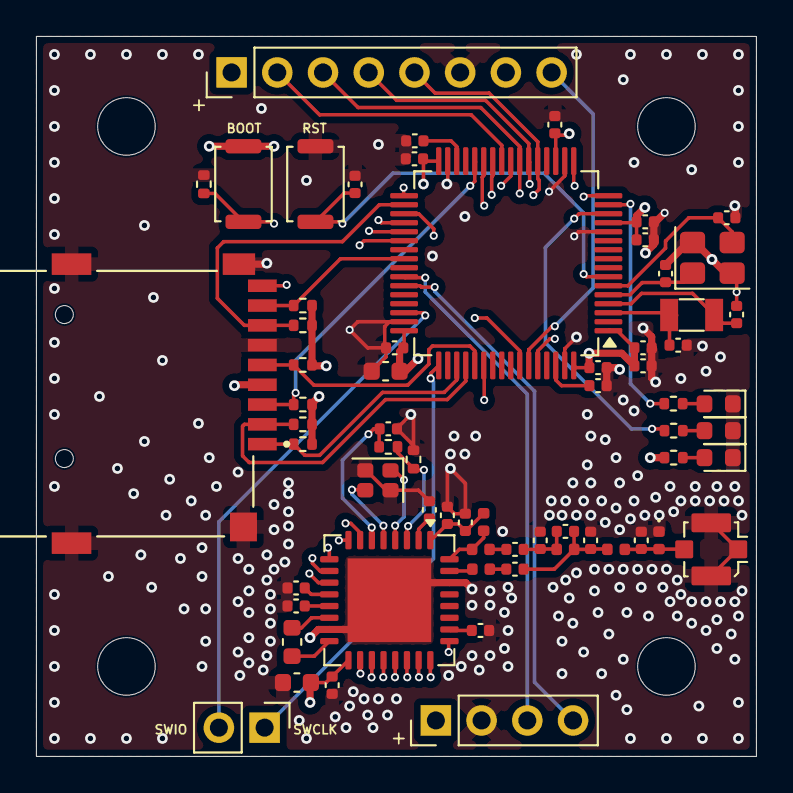
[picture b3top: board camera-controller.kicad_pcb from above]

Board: 4 copper layers, 40.0 x 40.0 mm, 65 parts (0 on the bottom side), 60 nets.

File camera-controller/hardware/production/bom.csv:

Designator,Footprint,Quantity,Value,LCSC Part #
"BOOT1, RESET1",SW_Push_SPST_NO_Alps_SKRK,2,SW_Push,
"C10, C13",0402,2,15pF,
"C11, C18, C20, C24, C25, C27, C29, C31, C32",0402,9,100nF,
"C12, C14, C9",0402,3,18pF,
"C19, C21, C34, C36",0402,4,1uF,
C2,0402,1,6.8pF,
"C26, C28, C35, C37",0402,4,2.2uF,
C3,0402,1,2.7pF,
"C30, C33",0603,2,4.7uF,
C38,0402,1,1nF,
C4,0402,1,1.1pF,
C5,0402,1,1.2pF,
C6,0402,1,2pF,
C7,0402,1,47pF,
D1,0402,1,D_TVS,
"D3, D4, D5",0603,3,LED,
J2,U.FL_Molex_MCRF_73412-0110_Vertical,1,Conn_Coaxial,
J3,PinHeader_1x04_P2.54mm_Vertical,1,Conn_01x04,
J4,PinHeader_1x08_P2.54mm_Vertical,1,Conn_01x08,
J5,CUI_MSD-4-A,1,Micro_SD_Card_Det1,
J6,PinHeader_1x02_P2.54mm_Vertical,1,Conn_01x02,
L1,0603,1,2.2uH,
L2,0402,1,18nH,
L3,0402,1,1.5nH,
L4,0402,1,1.6nH,
L5,0402,1,1.1nH,
L7,0402,1,2.4nH,
"R10, R3, R5, R6, R7, R8, R9",0402,7,10K,
"R11, R12, R13",0402,3,1.2K,
R4,0402,1,120K,
TH1,0402,1,ERT-J0ER104F,
U1,LQFP-64_10x10mm_P0.5mm,1,STM32H523RCTx,
U2,QFN-32-1EP_7x7mm_P0.65mm_EP4.65x4.65mm,1,LR2021,
Y1,Crystal_SMD_3215-2Pin_3.2x1.5mm,1,32.768MHz,
Y2,Crystal_SMD_3225-4Pin_3.2x2.5mm,1,24MHz,
Y3,Crystal_SMD_2016-4Pin_2.0x1.6mm,1,32MHz 10pF,
